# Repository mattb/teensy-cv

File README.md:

An opamp board with attenuating pots on inputs to:

* scale -5/+5V control voltage signals down to a voltage-referenced 0-2.5v range for reading by a Teensy's ADCs.
* scale up output from Teensy's DAC (and a Teensy PWM output with a low-pass RC filter) to -5/+5V range.

Note: output op amp configuration is inverting, which must be compensated for in code.

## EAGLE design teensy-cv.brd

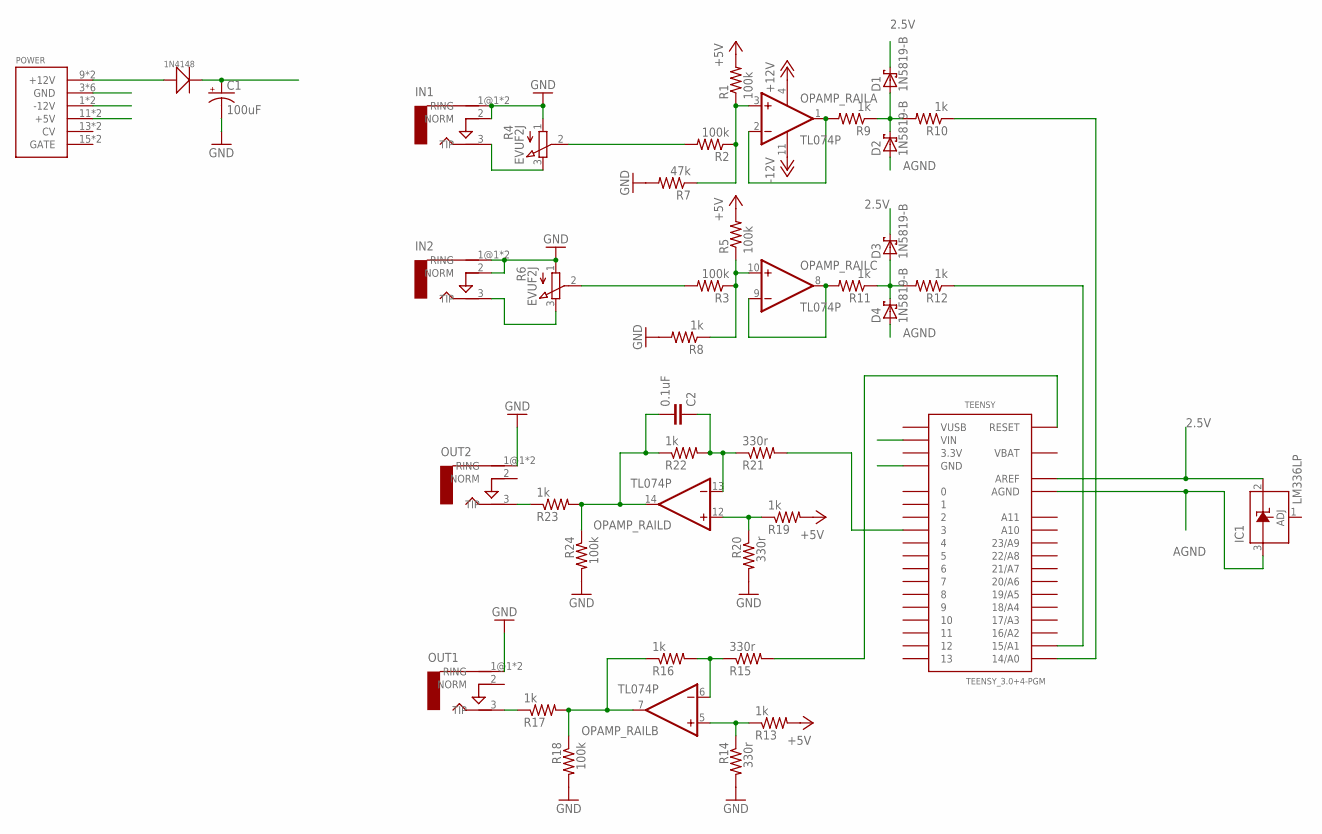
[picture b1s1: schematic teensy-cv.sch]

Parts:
1N4148: DIODE'1N4148'; DO-35
C1: 100uF; E2-4
C2: 0.1uF; C5B3
D1, D2, D3, D4: 1N5819-B; DO41-7.6
IC1: LM336LP; TO92
IN1, IN2: AUDIO-JACKERTHENVAR; ERTHENVAR-JACK
OPAMP_RAIL: TL074P; DIL14
OUT1, OUT2: AUDIO-JACKERTHENVAR; ERTHENVAR-JACK
POWER: POWER; POWER_16
R1, R2, R3, R5, R18, R24: 100k; 0207/7
R4, R6: EVUF2J; EVUFXJ
R7: 47k; 0207/7
R8, R9, R10, R11, R12, R13, R16, R17, R19, R22, R23: 1k; 0207/7
R14, R15, R20, R21: 330r; 0207/7
TEENSY: TEENSY_3.0+4-PGM

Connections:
1N4148: 1N4148.A (+), POWER.9 (+12V), POWER.10 (+12V)
2.5V: D1.C, D3.C, IC1.2 (C), TEENSY.AREF
3.3V: TEENSY.3.3V, TEENSY.3.3V1 (3.3V)
+5V: POWER.11 (+5V), POWER.12 (+5V), R1.2, R5.2, R13.2, R19.2, TEENSY.VIN
+12V: 1N4148.C (-), C1.+, OPAMP_RAIL.4 (V+)
-12V: OPAMP_RAIL.11 (V-), POWER.1 (-12V), POWER.2 (-12V)
AGND: D2.A, D4.A, IC1.3 (A), TEENSY.AGND
GND: C1.-, IN1.1@1 (RING), IN1.1@2 (RING), IN1.2 (NORM), IN2.1@1 (RING), IN2.1@2 (RING), IN2.2 (NORM), OUT1.1@1 (RING), OUT1.1@2 (RING), OUT2.1@1 (RING), OUT2.1@2 (RING), POWER.3 (GND), POWER.4 (GND), POWER.5 (GND), POWER.6 (GND), POWER.7 (GND), POWER.8 (GND), R4.1 (A), R6.1 (A), R7.2, R8.2, R14.2, R18.2, R20.2, R24.2, TEENSY.GND, TEENSY.GND1 (GND)
unnamed: R2.2, R4.2 (S)
unnamed: OPAMP_RAIL.1 (OUT), OPAMP_RAIL.2 (-IN), R9.2
unnamed: OPAMP_RAIL.3 (+IN), R1.1, R2.1, R7.1
unnamed: IN1.3 (TIP), R4.3 (E)
unnamed: D1.A, D2.C, R9.1, R10.2
unnamed: R10.1, TEENSY.14/A0
unnamed: IN2.3 (TIP), R6.3 (E)
unnamed: R3.2, R6.2 (S)
unnamed: OPAMP_RAIL.10 (+IN), R3.1, R5.1, R8.1
unnamed: OPAMP_RAIL.8 (OUT), OPAMP_RAIL.9 (-IN), R11.2
unnamed: D3.A, D4.C, R11.1, R12.2
unnamed: R12.1, TEENSY.15/A1
unnamed: OPAMP_RAIL.5 (+IN), R13.1, R14.1
unnamed: OPAMP_RAIL.6 (-IN), R15.1, R16.2
unnamed: OPAMP_RAIL.7 (OUT), R16.1, R17.2, R18.1
unnamed: OPAMP_RAIL.12 (+IN), R19.1, R20.1
unnamed: R15.2, TEENSY.RESET
unnamed: OUT1.3 (TIP), R17.1
unnamed: C2.1, OPAMP_RAIL.13 (-IN), R21.1, R22.2
unnamed: C2.2, OPAMP_RAIL.14 (OUT), R22.1, R23.2, R24.1
unnamed: R21.2, TEENSY.3
unnamed: OUT2.3 (TIP), R23.1
VBAT: TEENSY.VBAT
VUSB: TEENSY.VUSB

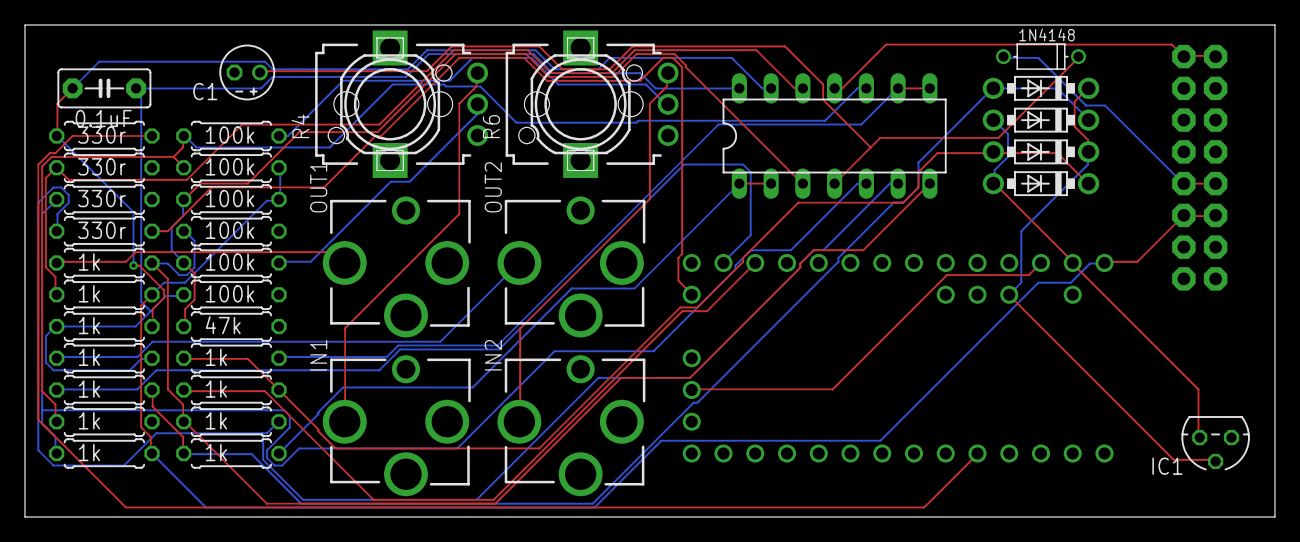
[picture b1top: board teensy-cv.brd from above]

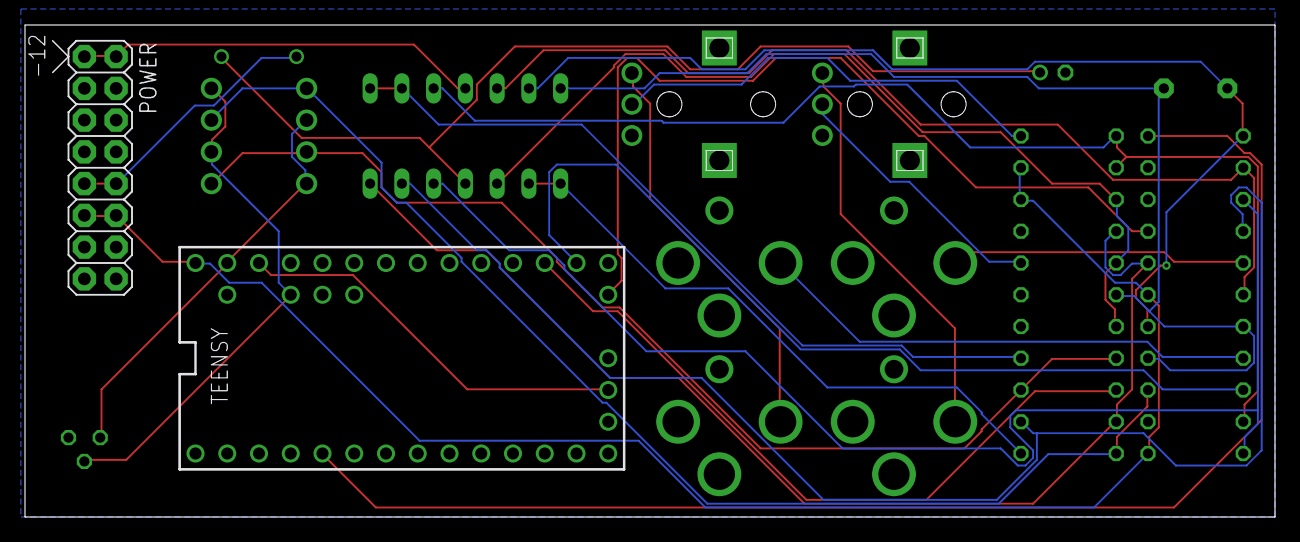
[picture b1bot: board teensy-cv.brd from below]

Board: 2 copper layers, 100.0 x 39.4 mm, 39 parts (2 on the bottom side), 30 nets.

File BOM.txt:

Qty Value               Device              Package          Parts                                               Description                                                                                                                                                                                                   
1                       DIODE'1N4148'       DO-35            1N4148                                                                                                                                                                                                                                                            
1   0.1uF               C5/3                C5B3             C2                                                  CAPACITOR                                                                                                                                                                                                     
6   100k                R-US_0207/7         0207/7           R1, R2, R3, R5, R18, R24                            RESISTOR, American symbol                                                                                                                                                                                     
1   100uF               CPOL-USE2-4         E2-4             C1                                                  POLARIZED CAPACITOR, American symbol                                                                                                                                                                          
4   1N5819-B            1N5819-B            DO41-7.6         D1, D2, D3, D4                                      1.0A SCHOTTKY BARRIER RECTIFIER                                                                                                                                                                               
11  1k                  R-US_0207/7         0207/7           R8, R9, R10, R11, R12, R13, R16, R17, R19, R22, R23 RESISTOR, American symbol                                                                                                                                                                                     
4   330r                R-US_0207/7         0207/7           R14, R15, R20, R21                                  RESISTOR, American symbol                                                                                                                                                                                     
1   47k                 R-US_0207/7         0207/7           R7                                                  RESISTOR, American symbol                                                                                                                                                                                     
4   AUDIO-JACKERTHENVAR AUDIO-JACKERTHENVAR ERTHENVAR-JACK   IN1, IN2, OUT1, OUT2                                Switching Mono 3.5mm Audio Jack from Erthenvar.                                                                                                                                                               
2   EVUF2J              EVUF2J              EVUFXJ           R4, R6                                              9 mm Square Rotary Potentiometers                                                                                                                                                                             
1   LM336LP             LM336LP             TO92             IC1                                                 2.5-V INTEGRATED REFERENCE CIRCUITS                                                                                                                                                                           
1   POWER               POWER               POWER_16         POWER                                                                                                                                                                                                                                                             
1   TEENSY_3.0+4-PGM    TEENSY_3.0+4-PGM    TEENSY_3.0+4-PGM TEENSY                                              
1   TL074P              TL074P              DIL14            OPAMP_RAIL                                          OP AMP

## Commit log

2015-11-11 init
2015-11-11 LICENSE
2015-11-11 Pics in README
2015-11-11 Add note on inverting output op amp.
